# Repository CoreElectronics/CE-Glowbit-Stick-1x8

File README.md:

# GlowBit™ Stick 1x8

This is the repo for the Core Electronics [GlowBit Stick 1x8](https://core-electronics.com.au/catalog/product/view/sku/ce08035).

## License
This project is open source - please review the LICENSE.md file for further licensing information.

If you have any technical questions, or concerns about licensing, please contact technical support on the [Core Electronics forums](https://forum.core-electronics.com.au/).

*\"GlowBit\" and the GlowBit logo are trademarks of Core Electronics Pty Ltd.*

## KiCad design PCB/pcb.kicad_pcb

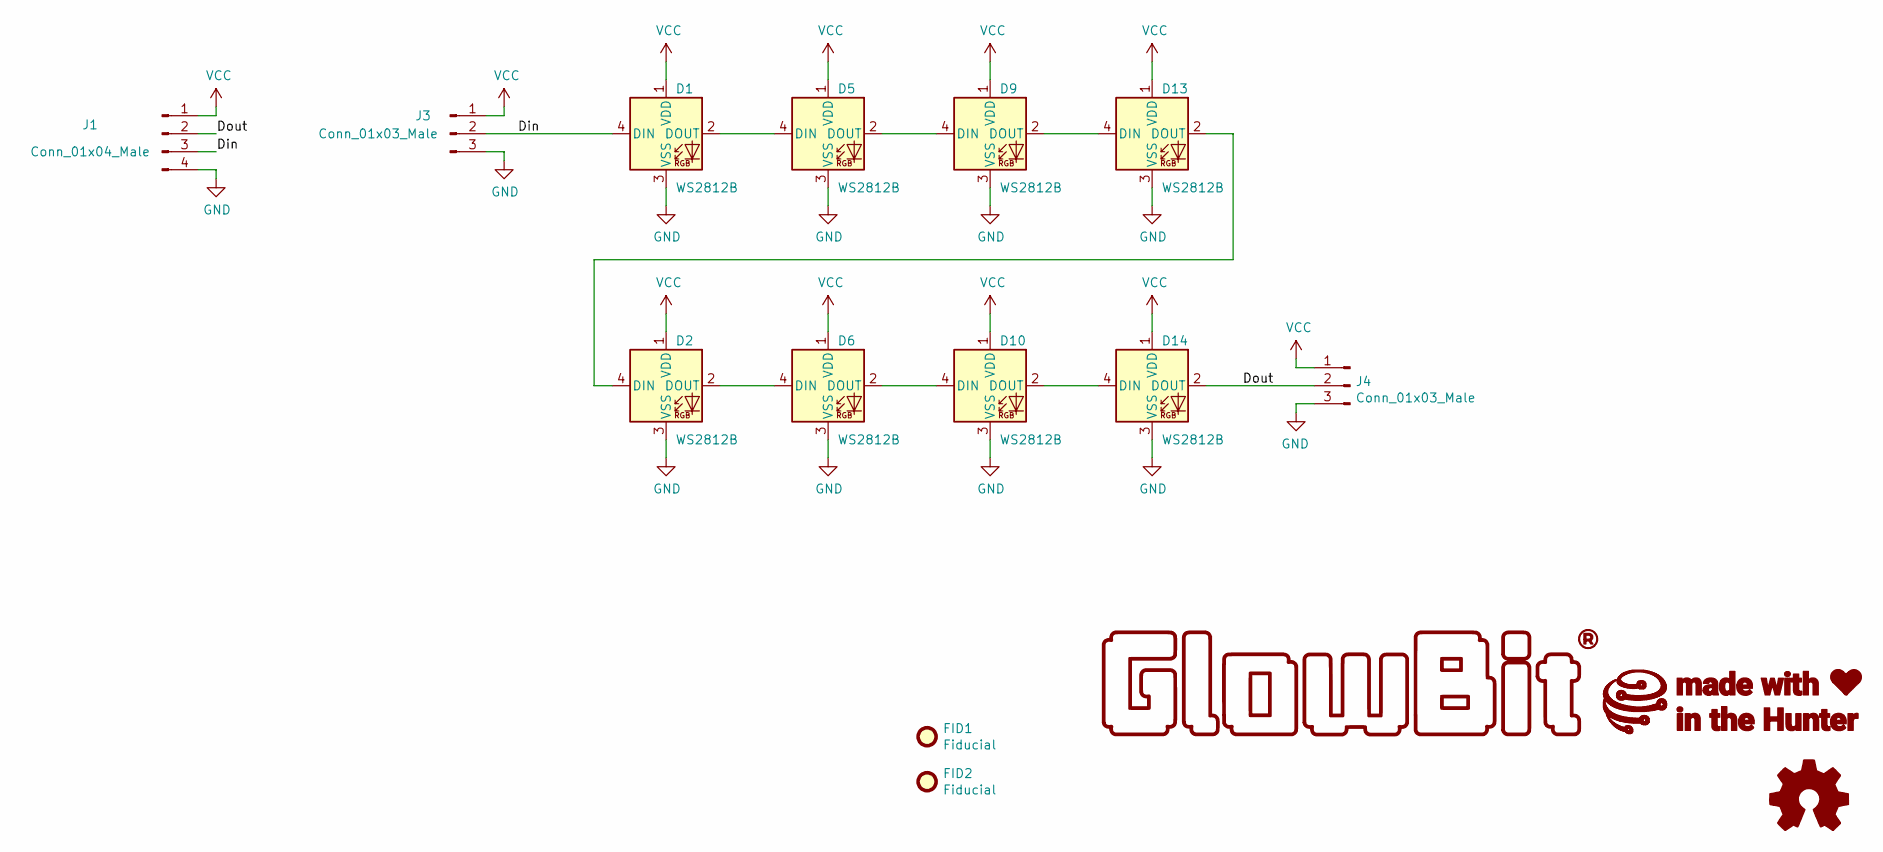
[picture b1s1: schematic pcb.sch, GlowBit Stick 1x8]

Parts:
D1, D2, D5, D6, D9, D10, D13, D14: WS2812B; LED_GlowBit_WS2812B_NoSilk
FID1, FID2: Fiducial; Fiducial_1mm_Mask2mm
J1: Conn_01x04_Male; PinHeader_1x04_P2.54mm_Vertical
J3, J4: Conn_01x03_Male; 3-pin-pads

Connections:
/Din: D1.4 (DIN), J1.3, J3.2
/Dout: D14.2 (DOUT), J1.2, J4.2
GND: D1.3 (VSS), D2.3 (VSS), D5.3 (VSS), D6.3 (VSS), D9.3 (VSS), D10.3 (VSS), D13.3 (VSS), D14.3 (VSS), J1.4, J3.3, J4.3
unnamed: D1.2 (DOUT), D5.4 (DIN)
unnamed: D2.2 (DOUT), D6.4 (DIN)
unnamed: D5.2 (DOUT), D9.4 (DIN)
unnamed: D10.2 (DOUT), D14.4 (DIN)
unnamed: D6.2 (DOUT), D10.4 (DIN)
unnamed: D2.4 (DIN), D13.2 (DOUT)
unnamed: D9.2 (DOUT), D13.4 (DIN)
VCC: D1.1 (VDD), D2.1 (VDD), D5.1 (VDD), D6.1 (VDD), D9.1 (VDD), D10.1 (VDD), D13.1 (VDD), D14.1 (VDD), J1.1, J3.1, J4.1

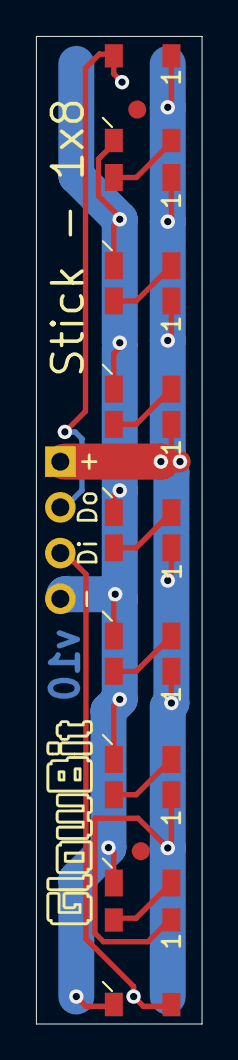
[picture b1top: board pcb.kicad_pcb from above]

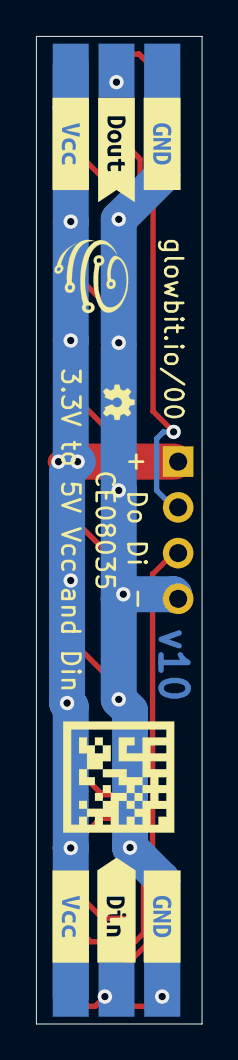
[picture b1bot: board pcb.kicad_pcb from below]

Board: 2 copper layers, 9.2 x 54.9 mm, 19 parts (8 on the bottom side), 11 nets.

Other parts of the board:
kibuzzard-6119FB4C, kibuzzard-6119FB06, kibuzzard-6119FB8F, kibuzzard-6119FB8F#2, kibuzzard-6119FBA7, kibuzzard-6119FBA7#2: G***; label

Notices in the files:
PCB/pcb.kicad_pcb:
License: CCASAv4.0 https://creativecommons.org/licenses/by-sa/4.0
